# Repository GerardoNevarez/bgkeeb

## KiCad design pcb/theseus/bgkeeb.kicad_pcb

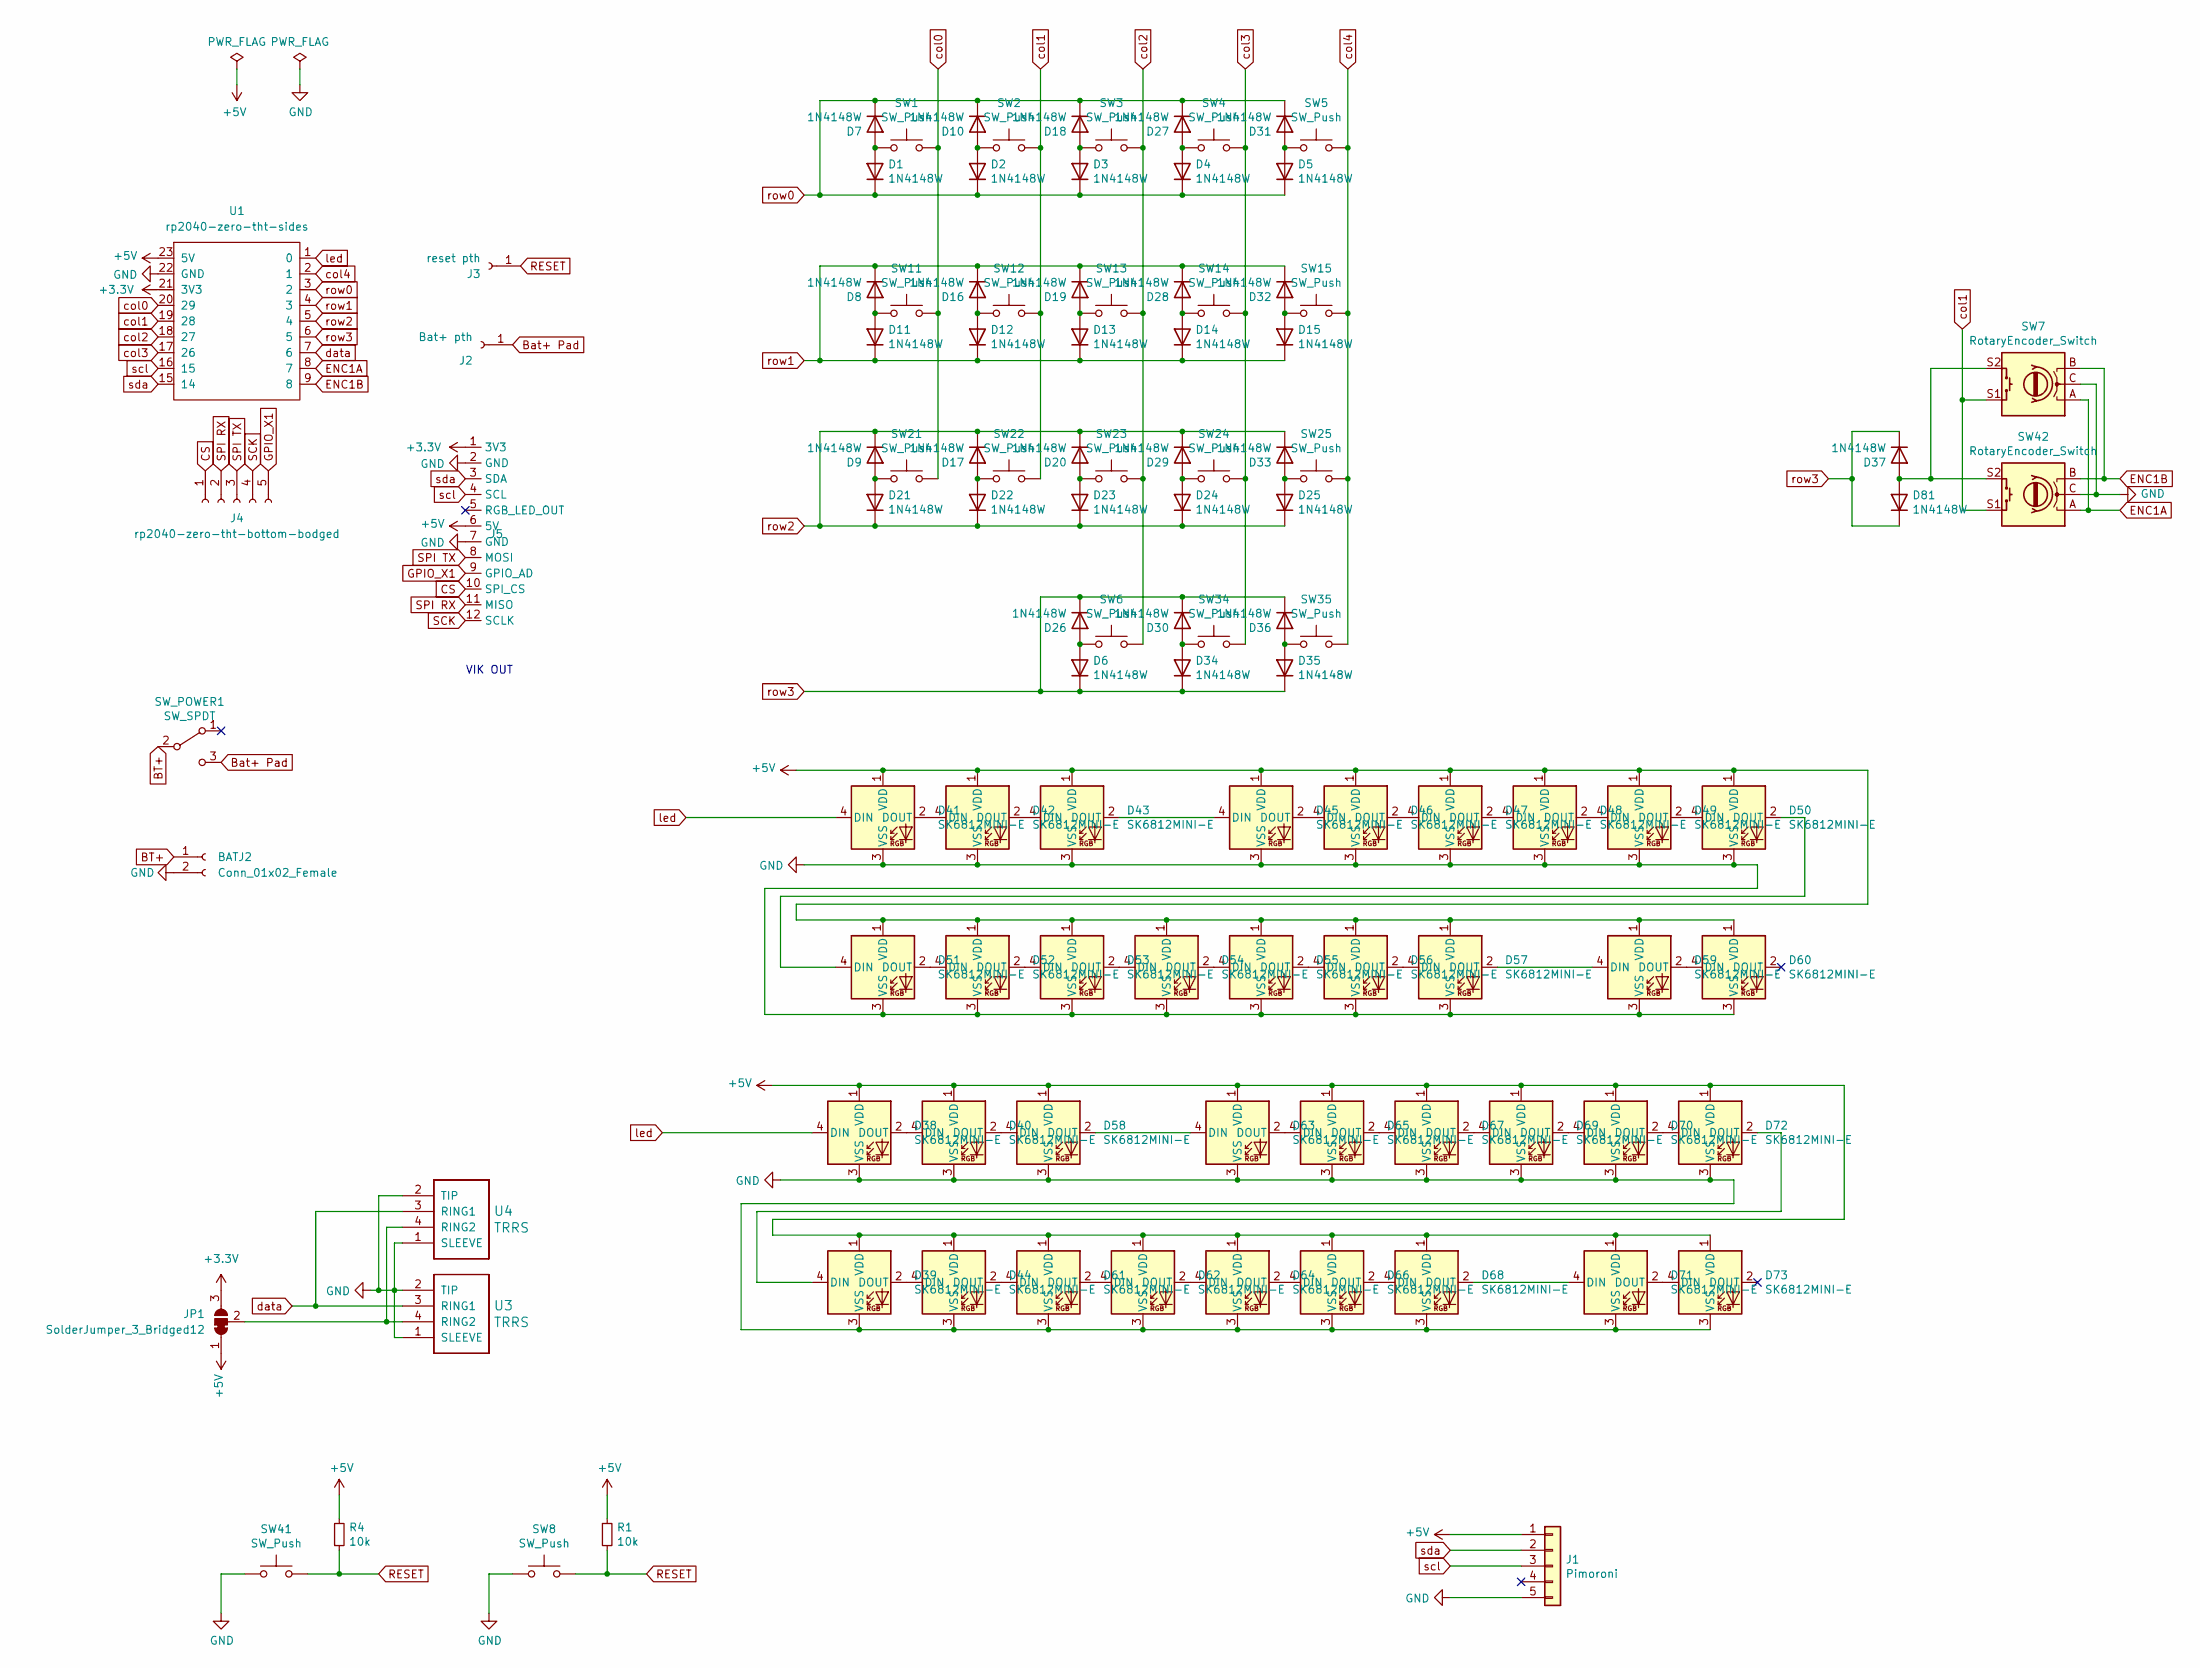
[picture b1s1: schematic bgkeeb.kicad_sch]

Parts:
BATJ2: Conn_01x02_Female; JST_PH_S2B-PH-K_1x02_P2.00mm_Horizontal_reversible
D1, D2, D3, D4, D5, D6, D7, D8, D9, D10, D11, D12, D13, D14, D15, D16, D17, D18, D19, D20, D21, D22, D23, D24, D25, D26, D27, D28, D29, D30, D31, D32, D33, D34, D35, D36, D37, D81: 1N4148W; D_SOD-123; LCSC C727110
D38, D39, D40, D41, D42, D43, D44, D45, D46, D47, D48, D49, D50, D51, D52, D53, D54, D55, D56, D57, D58, D59, D60, D61, D62, D63, D64, D65, D66, D67, D68, D69, D70, D71, D72, D73: SK6812MINI-E; MX_SK6812MINI-E
J1: Pimoroni; pimoroni
J2: Bat+ pth; PinSocket_1x01_P2.54mm_Vertical
J3: reset pth; PinSocket_1x01_P2.54mm_Vertical
J4: rp2040-zero-tht-bottom-bodged; PinSocket_1x05_P2.54mm_Vertical
J5: vik-connector-horizontal
JP1: SolderJumper_3_Bridged12; SolderJumper-3_P1.3mm_Bridged12_Pad1.0x1.5mm_NumberLabels
R1, R4: 10k; R_0805_2012Metric; LCSC C17414
SW1, SW2, SW3, SW4, SW5, SW6, SW11, SW12, SW13, SW14, SW15, SW21, SW22, SW23, SW24, SW25, SW34, SW35: SW_Push; SW_PG1350_reversible
SW7, SW42: RotaryEncoder_Switch; RotaryEncoder_EC11-no-legs
SW8, SW41: SW_Push; SKQG-1155865
SW_POWER1: SW_SPDT; SW_SPDT_PCM12_reversible
U1: rp2040-zero-tht-sides; rp2040-zero-tht-nocut
U3, U4: TRRS; TRRS-PJ-320A

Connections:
+3.3V: J5.1 (3V3), JP1.3 (B), U1.21 (3V3)
+5V: D38.1 (VDD), D39.1 (VDD), D40.1 (VDD), D41.1 (VDD), D42.1 (VDD), D43.1 (VDD), D44.1 (VDD), D45.1 (VDD), D46.1 (VDD), D47.1 (VDD), D48.1 (VDD), D49.1 (VDD), D50.1 (VDD), D51.1 (VDD), D52.1 (VDD), D53.1 (VDD), D54.1 (VDD), D55.1 (VDD), D56.1 (VDD), D57.1 (VDD), D58.1 (VDD), D59.1 (VDD), D60.1 (VDD), D61.1 (VDD), D62.1 (VDD), D63.1 (VDD), D64.1 (VDD), D65.1 (VDD), D66.1 (VDD), D67.1 (VDD), D68.1 (VDD), D69.1 (VDD), D70.1 (VDD), D71.1 (VDD), D72.1 (VDD), D73.1 (VDD), J1.1, J5.6 (5V), JP1.1 (A), R1.1, R4.1, U1.23 (5V)
BT+: SW_POWER1.2 (B); also elsewhere on the board
Bat+ Pad: J2.1, SW_POWER1.3 (C)
CS: J4.1 (Pin_14), J5.10 (SPI_CS)
ENC1A: SW7.A, SW42.A, U1.8 (7)
ENC1B: SW7.B, SW42.B, U1.9 (8)
GND: D38.3 (VSS), D39.3 (VSS), D40.3 (VSS), D41.3 (VSS), D42.3 (VSS), D43.3 (VSS), D44.3 (VSS), D45.3 (VSS), D46.3 (VSS), D47.3 (VSS), D48.3 (VSS), D49.3 (VSS), D50.3 (VSS), D51.3 (VSS), D52.3 (VSS), D53.3 (VSS), D54.3 (VSS), D55.3 (VSS), D56.3 (VSS), D57.3 (VSS), D58.3 (VSS), D59.3 (VSS), D60.3 (VSS), D61.3 (VSS), D62.3 (VSS), D63.3 (VSS), D64.3 (VSS), D65.3 (VSS), D66.3 (VSS), D67.3 (VSS), D68.3 (VSS), D69.3 (VSS), D70.3 (VSS), D71.3 (VSS), D72.3 (VSS), D73.3 (VSS), J1.5, J5.2 (GND), J5.7 (GND), SW7.C, SW8.1, SW41.1, SW42.C, U1.22 (GND), U3.1 (SLEEVE), U3.2 (TIP), U4.1 (SLEEVE), U4.2 (TIP); also elsewhere on the board
GPIO_X1: J4.5 (Pin_10), J5.9 (GPIO_AD)
unnamed: D1.2 (A), D7.2 (A), SW1.1
unnamed: D2.2 (A), D10.2 (A), SW2.1
unnamed: D8.2 (A), D11.2 (A), SW11.1
unnamed: D12.2 (A), D16.2 (A), SW12.1
unnamed: D13.2 (A), D19.2 (A), SW13.1
unnamed: D14.2 (A), D28.2 (A), SW14.1
unnamed: D15.2 (A), D32.2 (A), SW15.1
unnamed: D17.2 (A), D22.2 (A), SW22.1
unnamed: D3.2 (A), D18.2 (A), SW3.1
unnamed: D20.2 (A), D23.2 (A), SW23.1
unnamed: D9.2 (A), D21.2 (A), SW21.1
unnamed: D24.2 (A), D29.2 (A), SW24.1
unnamed: D25.2 (A), D33.2 (A), SW25.1
unnamed: D6.2 (A), D26.2 (A), SW6.1
unnamed: D4.2 (A), D27.2 (A), SW4.1
unnamed: D30.2 (A), D34.2 (A), SW34.1
unnamed: D5.2 (A), D31.2 (A), SW5.1
unnamed: D35.2 (A), D36.2 (A), SW35.1
unnamed: D37.2 (A), D81.2 (A), SW7.S2, SW42.S2
unnamed: D38.2 (DOUT), D40.4 (DIN)
unnamed: D39.4 (DIN), D72.2 (DOUT)
unnamed: D39.2 (DOUT), D44.4 (DIN)
unnamed: D40.2 (DOUT), D58.4 (DIN)
unnamed: D41.2 (DOUT), D42.4 (DIN)
unnamed: D42.2 (DOUT), D43.4 (DIN)
unnamed: D43.2 (DOUT), D45.4 (DIN)
unnamed: D44.2 (DOUT), D61.4 (DIN)
unnamed: D45.2 (DOUT), D46.4 (DIN)
unnamed: D46.2 (DOUT), D47.4 (DIN)
unnamed: D47.2 (DOUT), D48.4 (DIN)
unnamed: D48.2 (DOUT), D49.4 (DIN)
unnamed: D49.2 (DOUT), D50.4 (DIN)
unnamed: D50.2 (DOUT), D51.4 (DIN)
unnamed: D51.2 (DOUT), D52.4 (DIN)
unnamed: D52.2 (DOUT), D53.4 (DIN)
unnamed: D53.2 (DOUT), D54.4 (DIN)
unnamed: D54.2 (DOUT), D55.4 (DIN)
unnamed: D55.2 (DOUT), D56.4 (DIN)
unnamed: D56.2 (DOUT), D57.4 (DIN)
unnamed: D57.2 (DOUT), D59.4 (DIN)
unnamed: D58.2 (DOUT), D63.4 (DIN)
unnamed: D59.2 (DOUT), D60.4 (DIN)
unnamed: D61.2 (DOUT), D62.4 (DIN)
unnamed: D62.2 (DOUT), D64.4 (DIN)
unnamed: D63.2 (DOUT), D65.4 (DIN)
unnamed: D64.2 (DOUT), D66.4 (DIN)
unnamed: D65.2 (DOUT), D67.4 (DIN)
unnamed: D66.2 (DOUT), D68.4 (DIN)
unnamed: D67.2 (DOUT), D69.4 (DIN)
unnamed: D68.2 (DOUT), D71.4 (DIN)
unnamed: D69.2 (DOUT), D70.4 (DIN)
unnamed: D70.2 (DOUT), D72.4 (DIN)
unnamed: D71.2 (DOUT), D73.4 (DIN)
unnamed: JP1.2 (C), U3.4 (RING2), U4.4 (RING2)
RESET: J3.1, R1.2, R4.2, SW8.2, SW41.2
SCK: J4.4 (Pin_11), J5.12 (SCLK)
SPI RX: J4.2 (Pin_13), J5.11 (MISO)
SPI TX: J4.3 (Pin_12), J5.8 (MOSI)
col0: SW1.2, SW11.2, SW21.2, U1.20 (29)
col1: SW2.2, SW7.S1, SW12.2, SW22.2, SW42.S1, U1.19 (28)
col2: SW3.2, SW6.2, SW13.2, SW23.2, U1.18 (27)
col3: SW4.2, SW14.2, SW24.2, SW34.2, U1.17 (26)
col4: SW5.2, SW15.2, SW25.2, SW35.2, U1.2 (1)
data: U1.7 (6), U3.3 (RING1), U4.3 (RING1)
led: D38.4 (DIN), D41.4 (DIN), U1.1 (0)
row0: D1.1 (K), D2.1 (K), D3.1 (K), D4.1 (K), D5.1 (K), D7.1 (K), D10.1 (K), D18.1 (K), D27.1 (K), D31.1 (K), U1.3 (2)
row1: D8.1 (K), D11.1 (K), D12.1 (K), D13.1 (K), D14.1 (K), D15.1 (K), D16.1 (K), D19.1 (K), D28.1 (K), D32.1 (K), U1.4 (3)
row2: D9.1 (K), D17.1 (K), D20.1 (K), D21.1 (K), D22.1 (K), D23.1 (K), D24.1 (K), D25.1 (K), D29.1 (K), D33.1 (K), U1.5 (4)
row3: D6.1 (K), D26.1 (K), D30.1 (K), D34.1 (K), D35.1 (K), D36.1 (K), D37.1 (K), D81.1 (K), U1.6 (5)
scl: J1.3, J5.4 (SCL), U1.16 (15)
sda: J1.2, J5.3 (SDA), U1.15 (14)

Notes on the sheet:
VIK OUT

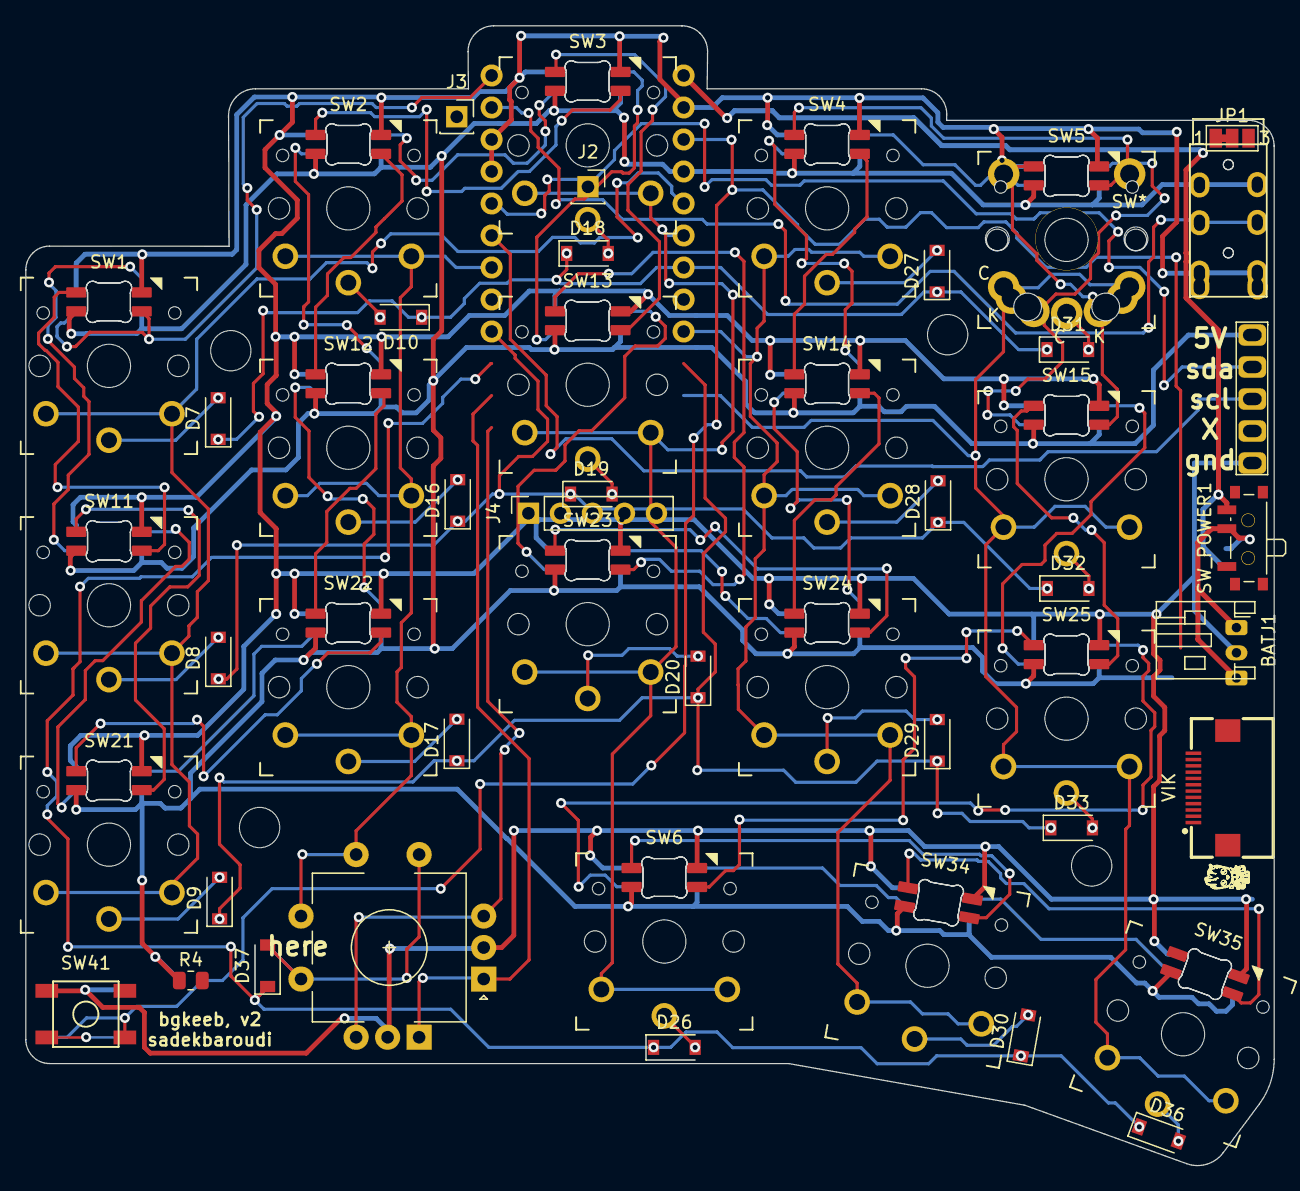
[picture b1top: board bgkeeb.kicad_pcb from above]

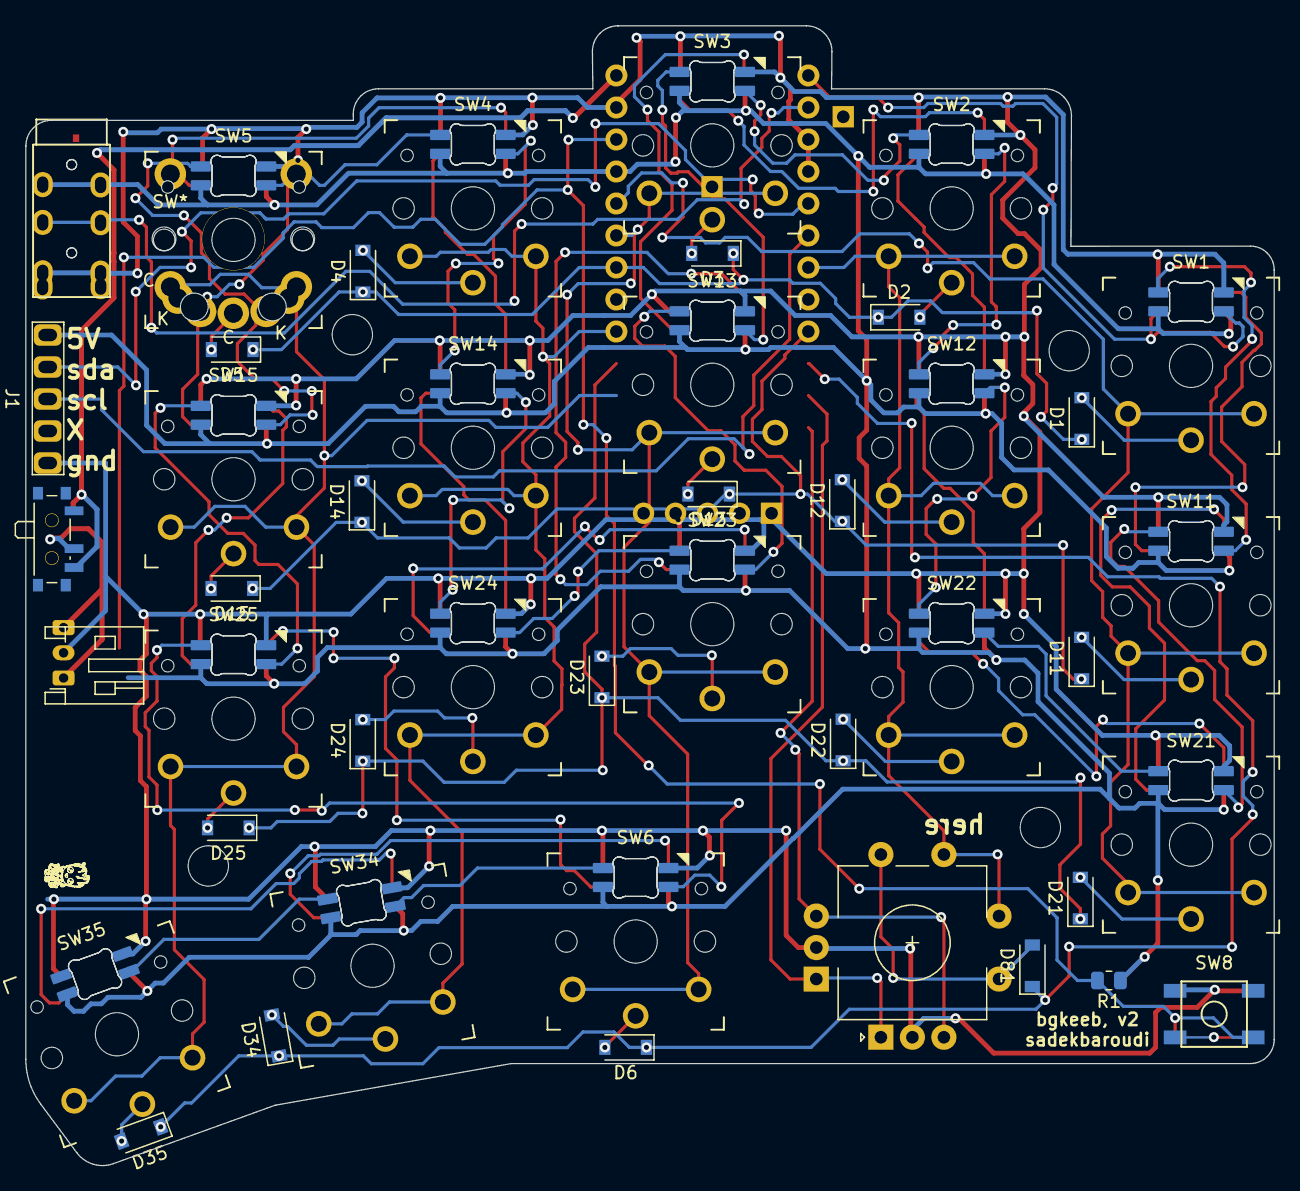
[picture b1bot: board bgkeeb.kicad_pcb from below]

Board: 2 copper layers, 99.1 x 90.5 mm, 110 parts (43 on the bottom side), 80 nets.

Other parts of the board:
BATJ1: Conn_01x02_Female; JST_PH_S2B-PH-K_1x02_P2.00mm_Horizontal_reversible
SW*: SW_PUSH; pg1353-ks27

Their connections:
BT+: BATJ1.1; also elsewhere on the board
GND: BATJ1.2; also elsewhere on the board

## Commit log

2023-12-02 Re-Start BgKeeb Theseus
2023-12-02 Libraries update
2023-12-02 Bye Promicro, Hello RP2040-Zero (with Xiao compatibility... almost!)
